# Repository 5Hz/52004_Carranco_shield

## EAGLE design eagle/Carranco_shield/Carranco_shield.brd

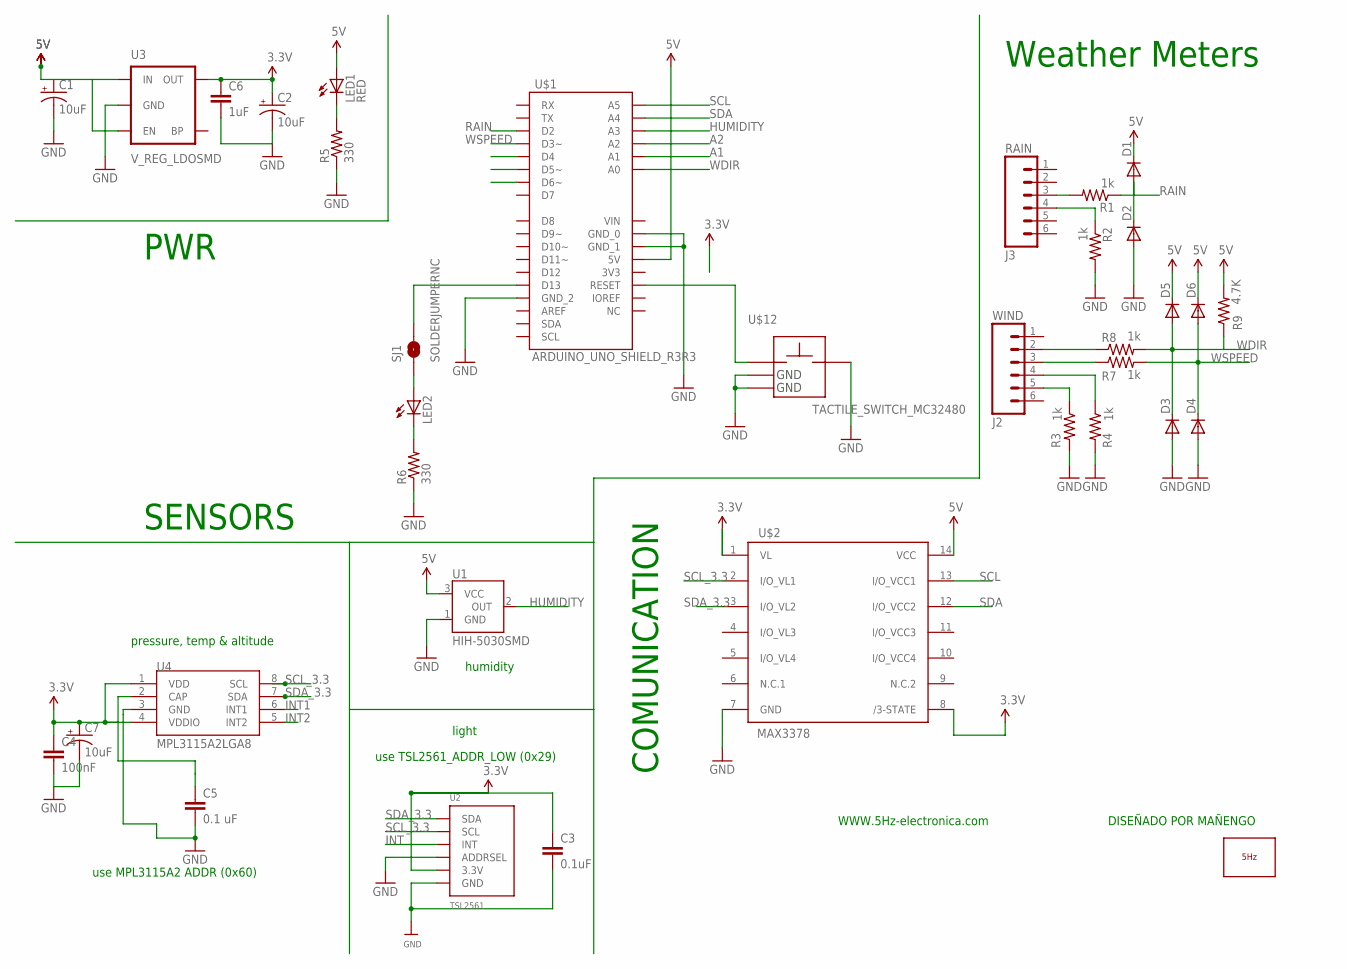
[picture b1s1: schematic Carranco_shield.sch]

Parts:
C1, C2, C7: 10uF; EIA3216
C3: 0.1uF; 0603-CAP
C4: 100nF; 0603-CAP
C5: 0.1 uF; 0603-CAP
C6: 1uF; 0603-CAP
D1, D2, D3, D4, D5, D6: DIODESOD; SOD-323
J2: WIND; RJ11-6
J3: RAIN; RJ11-6
LED1: RED; LED-0603
LED2: LED0603; LED-0603
LOGO1: LOGO_5HZ_H_20MM; 5HZ_LOGO_H_20MM
R1, R2, R3, R4, R7, R8: 1k; 0603-RES
R5, R6: 330; 0603-RES
R9: 4.7K; 0603-RES
SJ1: SOLDERJUMPERNC; SJ_2S
U1: HIH-5030SMD; HIH-5030
U2: TSL2561; TSL2561_FN
U3: V_REG_LDOSMD; SOT23-5
U4: MPL3115A2LGA8; LGA8
U$1: ARDUINO_UNO_SHIELD_R3R3; UNO_R3_SHIELD_HOLES_NO_SILK
U$2: MAX3378; TSSOP14
U$12: TACTILE_SWITCH_MC32480; MC32840

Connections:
3.3V: C2.A (+), C3.1, C4.1, C6.1, C7.A (+), U2.VDD (3.3V), U3.5 (OUT), U4.1 (VDD), U4.4 (VDDIO), U$2.1 (VL), U$2.8 (/3-STATE)
5V: C1.A (+), D1.1 (C), D5.1 (C), D6.1 (C), LED1.A, R9.2, U1.3 (VCC), U3.1 (IN), U3.3 (EN), U$1.5V, U$2.14 (VCC)
A1: U$1.A1
A2: U$1.A2
GND: C1.C (-), C2.C (-), C3.2, C4.2, C5.2, C6.2, C7.C (-), D2.2 (A), D3.2 (A), D4.2 (A), R2.2, R3.2, R4.2, R5.1, R6.1, U1.1 (GND), U2.ADR (ADDRSEL), U2.VSS (GND), U3.2 (GND), U4.3 (GND), U$1.GND_0, U$1.GND_1, U$1.GND_2, U$2.7 (GND), U$12.B, U$12.GND@1 (GND), U$12.GND@2 (GND)
HUMIDITY: U1.2 (OUT), U$1.A3
INT: U2.INT
INT1: U4.6 (INT1)
INT2: U4.5 (INT2)
unnamed: U$1.RES (RESET), U$12.A@1 (A)
unnamed: C5.1, U4.2 (CAP)
unnamed: J3.3, R1.2
unnamed: J3.4, R2.1
unnamed: J2.5, R3.1
unnamed: J2.4, R4.1
unnamed: J2.3, R7.1
unnamed: J2.2, R8.1
unnamed: LED2.C, R6.2
unnamed: LED2.A, SJ1.1
unnamed: LED1.C, R5.2
unnamed: SJ1.2, U$1.D13
RAIN: D1.2 (A), D2.1 (C), R1.1, U$1.D2
SCL: U$1.A5, U$2.13 (I/O_VCC1)
SCL_3.3: U2.CLK (SCL), U4.8 (SCL), U$2.2 (I/O_VL1)
SDA: U$1.A4, U$2.12 (I/O_VCC2)
SDA_3.3: U2.DATA (SDA), U4.7 (SDA), U$2.3 (I/O_VL2)
WDIR: D3.1 (C), D5.2 (A), R8.2, R9.1, U$1.A0
WSPEED: D4.1 (C), D6.2 (A), R7.2, U$1.D3 (D3~)

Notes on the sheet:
PWR
SENSORS
COMUNICATION
DISEÑADO POR MAÑENGO
WWW.5Hz-electronica.com
pressure, temp & altitude
humidity
light
use TSL2561_ADDR_LOW (0x29)
use MPL3115A2 ADDR (0x60)
Weather Meters

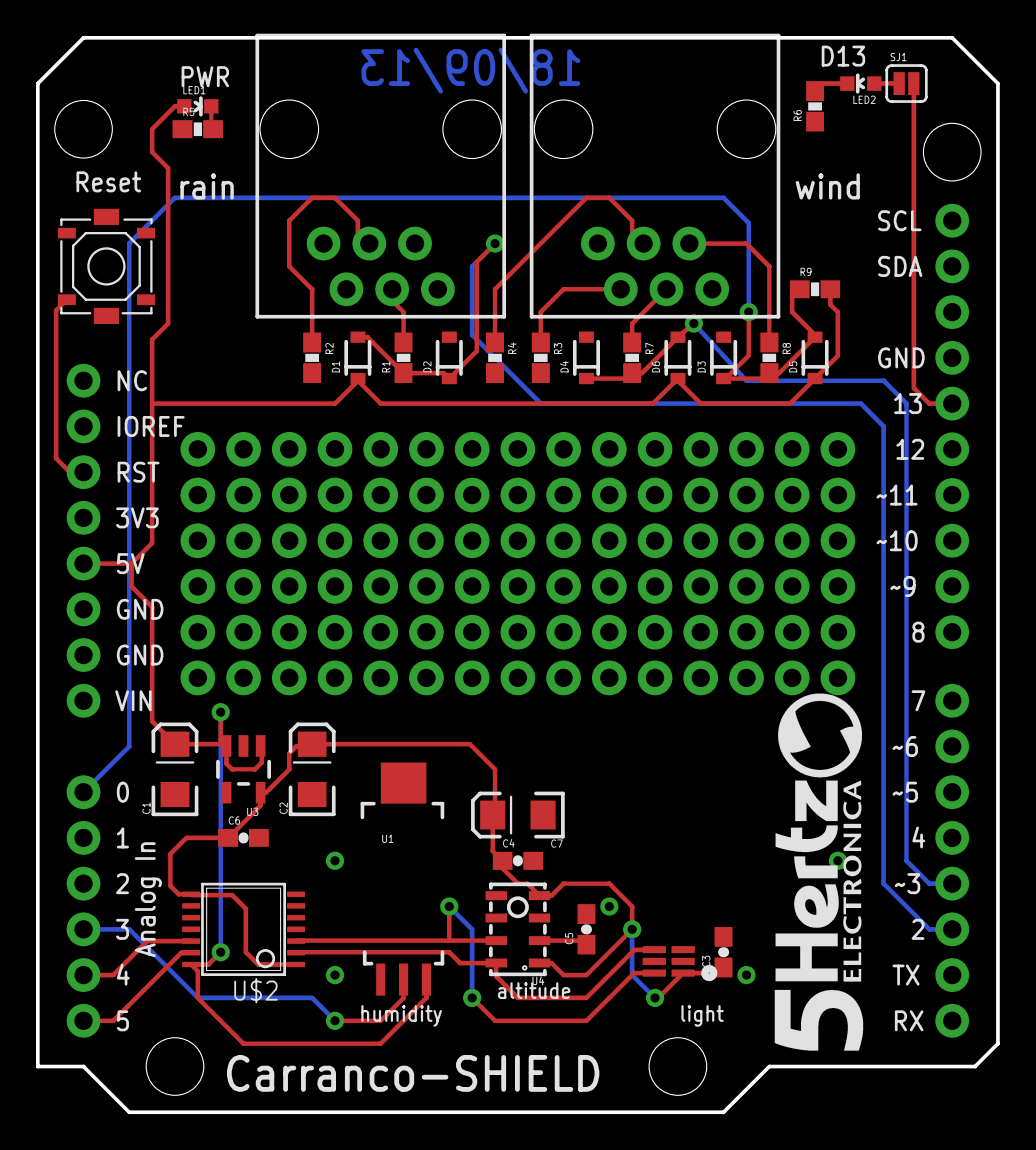
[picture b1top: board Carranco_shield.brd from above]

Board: 2 copper layers, 53.3 x 59.7 mm, 35 parts (0 on the bottom side), 23 nets.

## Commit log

2014-01-09 creacion
2014-01-09 Organización

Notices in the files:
parts and their libraries:
SparkFun-Sensors: Licensing: CC v3.0 Share-Alike You are welcome to use this library for commercial purposes.
